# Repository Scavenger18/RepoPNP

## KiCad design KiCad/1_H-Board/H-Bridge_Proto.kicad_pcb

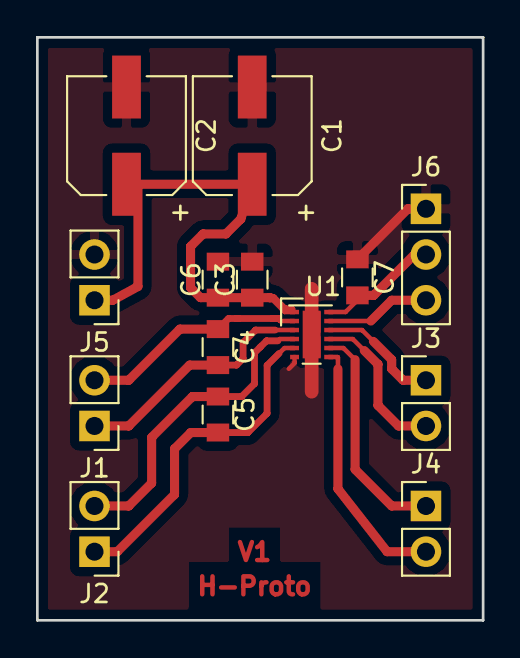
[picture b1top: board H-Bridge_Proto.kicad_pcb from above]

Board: 2 copper layers, 24.8 x 32.4 mm, 14 parts (0 on the bottom side), 12 nets.

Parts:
C1, C2: 220u; CP_Elec_6.3x7.7
C3: 1u; C_0805
C4, C5: 3n3; C_0805
C6, C7: 100n; C_0805
J1, J2, J3, J4, J5: Conn_01x02; Pin_Header_Straight_1x02_Pitch2.54mm
J6: Conn_01x03; Pin_Header_Straight_1x03_Pitch2.54mm
U1: DRV8835; WSON-12-1EP_3x2mm_Pitch0.5mm

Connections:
+3V3: C7.2, J6.2, U1.12
+8V: C1.1, C2.1, C3.1, C6.1, J5.1, U1.1
/Dir_A: J3.1, U1.10
/Dir_B: J4.1, U1.8
/PWM_A: J3.2, U1.9
/PWM_B: J4.2, U1.7
GND: C1.2, C2.2, C3.2, C6.2, C7.1, J5.2, J6.1, U1.6, U1.13
unnamed: C4.1, J1.2, U1.2
unnamed: C4.2, J1.1, U1.3
unnamed: C5.1, J2.2, U1.4
unnamed: C5.2, J2.1, U1.5
unnamed: J6.3, U1.11

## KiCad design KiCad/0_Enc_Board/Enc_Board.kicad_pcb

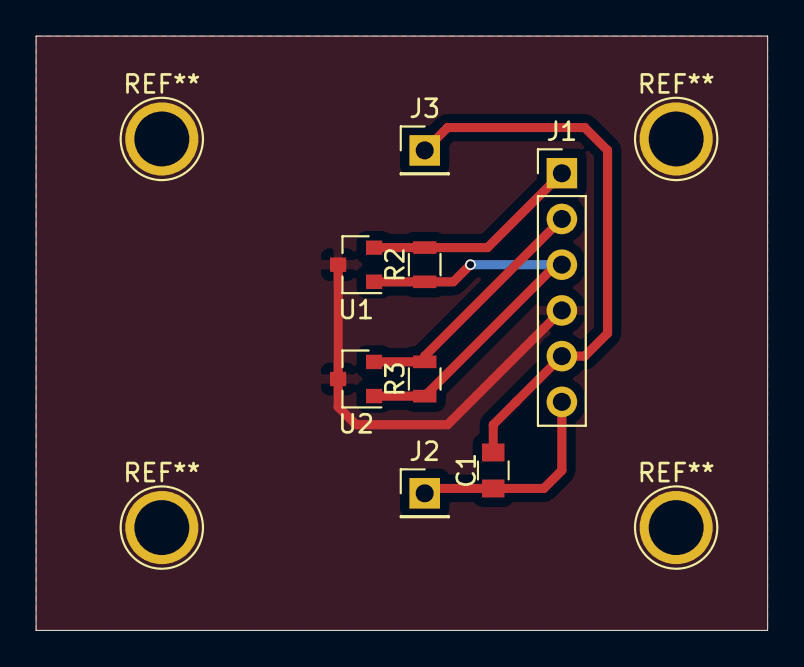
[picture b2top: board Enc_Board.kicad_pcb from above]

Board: 2 copper layers, 40.6 x 33.0 mm, 8 parts (0 on the bottom side), 6 nets.

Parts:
C1: 3n3; C_0805
J1: Conn_01x06; Pin_Header_Straight_1x06_Pitch2.54mm
J2: Mot+; Pin_Header_Straight_1x01_Pitch2.54mm
J3: Mot-; Pin_Header_Straight_1x01_Pitch2.54mm
R2, R3: N/P; R_0805
U1, U2: DRV5013; SOT-23

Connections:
+3V3: J1.3, R2.1, R3.1, U1.1, U2.1
/Enc_L_A: J1.1, R2.2, U1.2
/Enc_L_B: J1.2, R3.2, U2.2
GND: J1.4, U1.3, U2.3
unnamed: C1.1, J1.6, J2.1
unnamed: C1.2, J1.5, J3.1

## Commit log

2018-03-06 Added Encoder and H-Bridge KiCad projects
2018-03-06 Finished H-Bridge PCB V1
2018-03-06 Added DRV8838 Datasheet
2018-03-08 Created H-Bridge CAM File
2018-03-13 added datasheets
2018-03-26 added sourcecode for tinyk22
2018-03-26 added datasheets and enc pcb
2018-04-03 added datasheet
2018-04-16 added datahseets and parts of tinyk22 code
2018-04-16 added K20 project
2018-04-16 changes to K22_V2 project
2018-04-16 changes to k20 project -> DaisyChain & LPressRev
2018-04-23 changed communication protocoll
2018-04-24 changed pins to PCB build
2018-05-06 moved tasks to respective source files
2018-05-08 changed gitignore
2018-05-14 updated code
2018-05-18 map file update
2018-05-19 reverse functionality enabled
2018-05-27 updated Feeder Project
2018-05-28 added TimeOut in Application FSM
2018-05-28 added commentary
2018-05-29 reorganized structure, cleanup
2018-05-29 added KiCad Projects
2018-05-29 added Init for Status-LED
2018-06-06 added Documentation
2018-06-06 added KDS feeders code
